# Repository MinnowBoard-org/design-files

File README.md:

# MinnowBoard.org Hardware Design Files

## PURPOSE:
The `/design-files` repository is the target folder for official [MinnowBoard.org] hardware design files. Such files may include: design schematics, printed circult board (PCB) design database(s), PCB gerber files, PCB manufacturing files, bill of materials (BOM), 3D models, mechanical step files, thermal models, multiple versions for different design tools, some firmware, CPLD code, FPGA code, etc. 

## LICENSING:
*All files are subject to the associated licensing stated within each directory.* [MinnowBoard.org] is founded with a goal for full open source, defaulting to [Creative Commons Attribution 4.0](https://creativecommons.org/licenses/by/4.0/) for hardware and [MIT](https://opensource.org/licenses/MIT) license for code....to let developers take the files and develop without licensing burden. We stick to this as much as possible. For a deep read, see MinnowBoard.org [Terms of Service and Intellectual Property Rights](https://www.minnowboard.org/terms-of-service). If you have questions, [Contact us.](https://www.minnowboard.org/help)

## SAFETY AND REGULATORY:
### The Disclaimer:
>The files for MinnowBoard reference designs do not guarantee regulatory compliance.  The developer is responsible for all aspects of regulatory evaluation, reporting and registration when modifying and/or incorporating any element of these reference designs into a host device.

### What it means:
Our goal is for developers to easily prototype their innovative idea with optimized MinnowBoard hardware/software/firmware, but this isn't the end goal. We ALSO want to enable developers to easily PRODUCTIZE and bring their idea to market. Such a product must meet the legal, safety, regulatory, commerce, etc, requirements for the target distribution geography. Thus, we spend extra time and effort to design our developer boards to already meet the electrical, EMI/EMC, safety, etc requirements for most global countries, and further, we test to those standards in licensed labs. We will often share the reports as reference baseline for developers considering design modifications. 
>Example: The current MinnowBoard target for EMI/EMC emissions in the United States is open board FCC Title 47 Part 15 Class B, which generally allows distribution to both commercial and residential environments. (Most developer boards are not even close to this).

*The Takeaway:* We do our best to minimize the effort required to achieve regulatory compliance on developer production design derivatives, but you are responsible for all aspects of regulatory compliance for your modification designs.

[MinnowBoard.org]: https://minnowboard.org/

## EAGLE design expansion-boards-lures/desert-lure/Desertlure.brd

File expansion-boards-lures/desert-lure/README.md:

# DesertLure
A lure for the MinnowBoard Max & MinnowBoard Turbot.  Copyright (C) 2015 Smallworks, LLC

This design is made with [EAGLE CAD](http://www.cadsoftusa.com/eagle-pcb-design-software/about-eagle/) 

This work is licensed under a Creative Commons Attribution-ShareAlike 4.0 International License
[  
*Licensing CC BY-SA 4.0*](http://creativecommons.org/licenses/by-sa/4.0/)

It may be used for Educational, Personal, or Commercial Use, provided you keep these notices,
attribution, and share-alike. When you apply these licenses to material you create, 
it meets the Freedom Defined definition of a "Free Cultural Work". 
Free cultural works are the ones that can be most readily used, shared, 
and remixed by others, and go furthest toward creating a commons of freely reusable materials.

-------------------------------------------------------------------------------------------

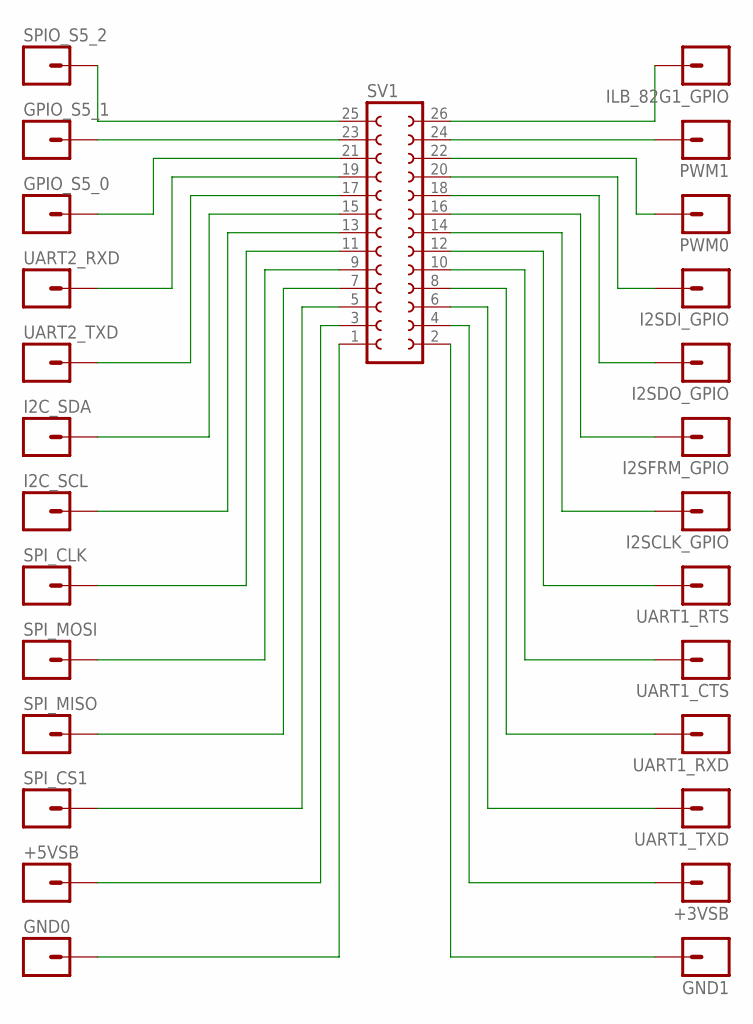
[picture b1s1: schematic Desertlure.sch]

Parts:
+3VSB, +5VSB: M01NOSILK-KIT; 1X01NS-KIT
GND0, GND1: M01NOSILK-KIT; 1X01NS-KIT
GPIO_S5_0, GPIO_S5_1: M01NOSILK-KIT; 1X01NS-KIT
I2C_SCL, I2C_SDA, I2SCLK_GPIO, I2SDI_GPIO, I2SDO_GPIO, I2SFRM_GPIO: M01NOSILK-KIT; 1X01NS-KIT
ILB_82G1_GPIO: M01NOSILK-KIT; 1X01NS-KIT
PWM0, PWM1: M01NOSILK-KIT; 1X01NS-KIT
SPIO_S5_2: M01NOSILK-KIT; 1X01NS-KIT
SPI_CLK: M01NOSILK-KIT; 1X01NS-KIT
SPI_CS1: M01NOSILK-KIT; 1X01NS-KIT
SPI_MISO: M01NOSILK-KIT; 1X01NS-KIT
SPI_MOSI: M01NOSILK-KIT; 1X01NS-KIT
SV1: FE13-2W
UART1_CTS, UART1_RTS, UART1_RXD, UART1_TXD, UART2_RXD, UART2_TXD: M01NOSILK-KIT; 1X01NS-KIT

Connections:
unnamed: GND0.1, SV1.1
unnamed: +5VSB.1, SV1.3
unnamed: SPI_CS1.1, SV1.5
unnamed: SPI_MISO.1, SV1.7
unnamed: SPI_MOSI.1, SV1.9
unnamed: SPI_CLK.1, SV1.11
unnamed: I2C_SCL.1, SV1.13
unnamed: I2C_SDA.1, SV1.15
unnamed: SV1.17, UART2_TXD.1
unnamed: SV1.19, UART2_RXD.1
unnamed: GPIO_S5_0.1, SV1.21
unnamed: GPIO_S5_1.1, SV1.23
unnamed: SPIO_S5_2.1, SV1.25
unnamed: GND1.1, SV1.2
unnamed: +3VSB.1, SV1.4
unnamed: SV1.6, UART1_TXD.1
unnamed: SV1.8, UART1_RXD.1
unnamed: SV1.10, UART1_CTS.1
unnamed: SV1.12, UART1_RTS.1
unnamed: I2SCLK_GPIO.1, SV1.14
unnamed: I2SFRM_GPIO.1, SV1.16
unnamed: I2SDO_GPIO.1, SV1.18
unnamed: I2SDI_GPIO.1, SV1.20
unnamed: PWM0.1, SV1.22
unnamed: PWM1.1, SV1.24
unnamed: ILB_82G1_GPIO.1, SV1.26

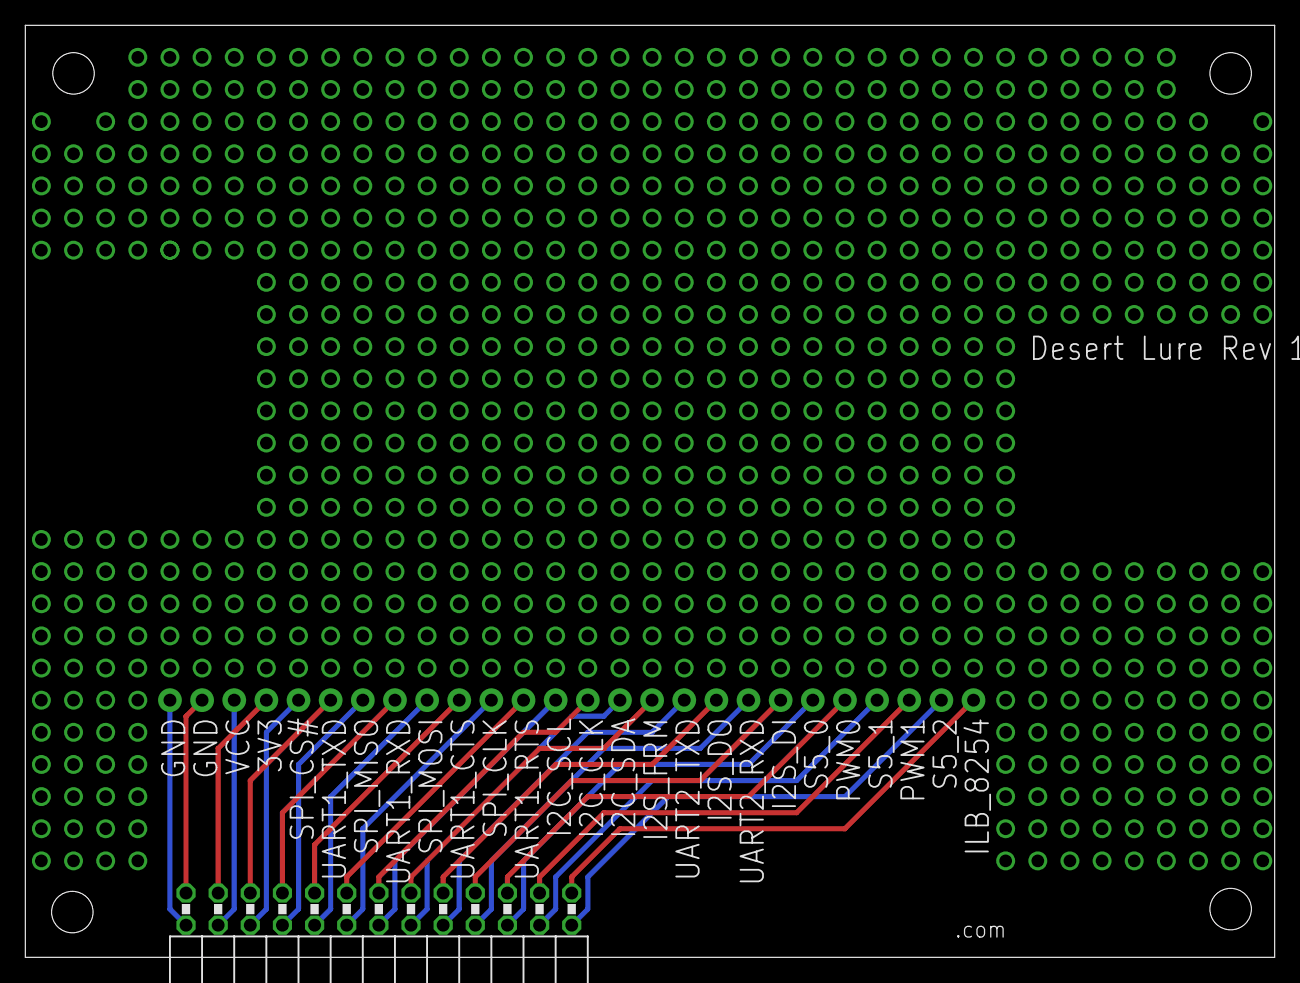
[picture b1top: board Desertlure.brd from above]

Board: 2 copper layers, 98.7 x 73.7 mm, 27 parts (0 on the bottom side), 26 nets.

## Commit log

2017-01-31 Update README.md
    initial
2017-01-31 MB3 upload
    MB3 upload
2017-01-31 Adding Turbot Quad Core placeholder
2017-01-31 ADI to post Dual-e design files.
2017-01-31 MB3 files placeholder
2017-02-01 new files
2017-02-01 Create License File guidance
2017-02-01 Update License Guidance
2017-02-01 Create license.md
    Replicated the license provided for PCB rev F200, originally open sourced at the old wiki.minnowboard.org.
2017-02-01 Create PCB-a2 license
    replicates license established for original release of files on old website wiki.minnowboard.org
2017-02-01 Create license.md
    Replicates license established with original release of files on wiki.minnowboard.org.
2017-02-08 Updated Readme to add CC-BY 4.0 URL
2017-02-08 Updated Readme CC-BY 4.0 URL
2017-02-09 lower case pcb rev directory
    that is it.
2017-02-10 MB v1 files from wiki
2017-02-10 Created license file that replicates original files release.
    License file created for rev-a of MinnowBoard-v1. This file exactly
    copies the license appearing on schematic pdf, and applies to all the
    PCB design files posted.
2017-02-23 new v1 guides from wiki
    new v1 guides from wiki
2017-03-06 new
    new
2017-03-06 moved
2017-03-06 removed duplicated sentence
2017-03-08 reflected owner name
2017-03-17 Add MB Brand Guidelines
    Add MB Brand Guidelines
2017-03-17 modify naming
2017-03-17 Revert "modify naming"
    This reverts commit 72a8703f290859ccc76ff0953185ee43d9a4af4e.
2017-03-17 license file add
    add
2017-03-17 rename
2017-03-17 license update
2017-03-29 GPS Lure repo link and readme
2017-04-17 Removed placeholder PCB folder
2017-04-18 moved Turbot A21 files under single Turbot dual folder
    moved Turbot A21 files under single Turbot dual folder. NO Content
    changes.
2017-04-18 Removed Duplicate license.md file for the F400-R302 pcb.
    removed duplicate license.md. Master license file for F400-R302 remains
    under the associated PCB folder containing the collatera.
2017-04-19 updated URL link to database file.
    updated URL link to database file. NO change to licensing verbiage.
2017-05-15 Fixed Typos and removed revisions from license files. Deleted duplicate license files from zips and directories.
2017-06-10 Typo fix on schematic file and PDF schematic.
    Typo fix on schematic file and PDF schematic, changed from Fish Feed
    Lure to Fish Food Lure.
2017-06-10 Big relay lure block terminal fix.
    Fixed wrong description of relay block terminal. Footprint is actually
    6.35mm in pitch instead of 9.52mm. Updated Schematic file, PDF
    schematic and BOM.
2017-08-08 adding files
2017-09-27 README.md: fix markdown formatting
    The markdown formatting of the README.md file was slightly incorrect causing the rendering to be broken. This fixes the formatting and also adds a couple of hyperlinks.
2017-10-04 .dxf file as provided by Len at ADI
    Mentor output to dxf.
2017-10-04 .dxf file addition
    Direct Mentor output to .dxf, as provided by Len at ADI Engineering.
2017-10-04 DXF Showing Mounting and Part Holes. Units are thousandths of an inch.
2017-10-23 Design for MinnowBoard Turbot fan less heatsink
    Design sketch for MinnowBoard Turbot B Dual-Core fan-less heatsink.
2017-10-23 Added sketch for MB Turbot Quad-Core fan-sink
    Design sketch for MinnowBoard Turbot Quad-Core fan based heat-sink.
2022-08-10 Add .gitattributes
2022-08-10 Update .gitattributes
    Add Cadence

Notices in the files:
parts and their libraries:
SparkFun-Connectors: Licensing: Creative Commons ShareAlike 4.0 International - https://creativecommons.org/licenses/by-sa/4.0
